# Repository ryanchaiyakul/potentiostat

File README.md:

# Potentiostat

I2BL potentiostat library and project.

# Goals

1. Create a library to easily program simple potentiostats for various voltammetry methods.
2. Create a collection of tools to develop future potentiostats.
3. Create a simulation suite to visualize and validate design decisions.

# Simulations

Go to the [README.md](CAD/LTSpice/README.md) in CAD/LTSpice folder.

# Tools

Go to the tools folder for a complete collection.

## CPE Models

Generate RC Train models of CPE elements to simulate how the readout circuit responds.

## PWL Voltammetry

Generate PWL files to pass into a voltage source to act as the DAC.

# Usage

```bash
# submodules are used in this repository for third party libraries
git clone --recurse-submodules git@github.com:ryanchaiyakul/potentiostat.git
```

1. Open the project in [VS Code](https://code.visualstudio.com/) with the [PlatformIO extension](https://marketplace.visualstudio.com/items?itemName=platformio.platformio-ide) installed.
2. Connect the Potentiostat to your computer by USB.
3. Navigate to the PlatformIO panel and click "Upload" or use the Command Palette (CNTL + SHIFT + P) and select "Upload".
4. Use the Serial Monitor in the terminal bar and select the baudrate of 230400.

# Features

- [x] Differential Pulse Voltammetry
- [x] Square Wave Voltammetry
- [ ] Cyclic Voltammetry
- [x] 300+ Hz SWV
- [ ] OTA Configuration
- [ ] EEPROM Persistent Configuration
- [ ] BLE Integration
- [x] Simple "Debug" Mode
- [x] Complete Analytics in "Debug" Mode
- [ ] Unit Testing Suite

# Development Guide

Create a valid class that inherits from Voltammetry defined in [Voltammetry.h](lib/Voltammetry/Voltammetry.h).

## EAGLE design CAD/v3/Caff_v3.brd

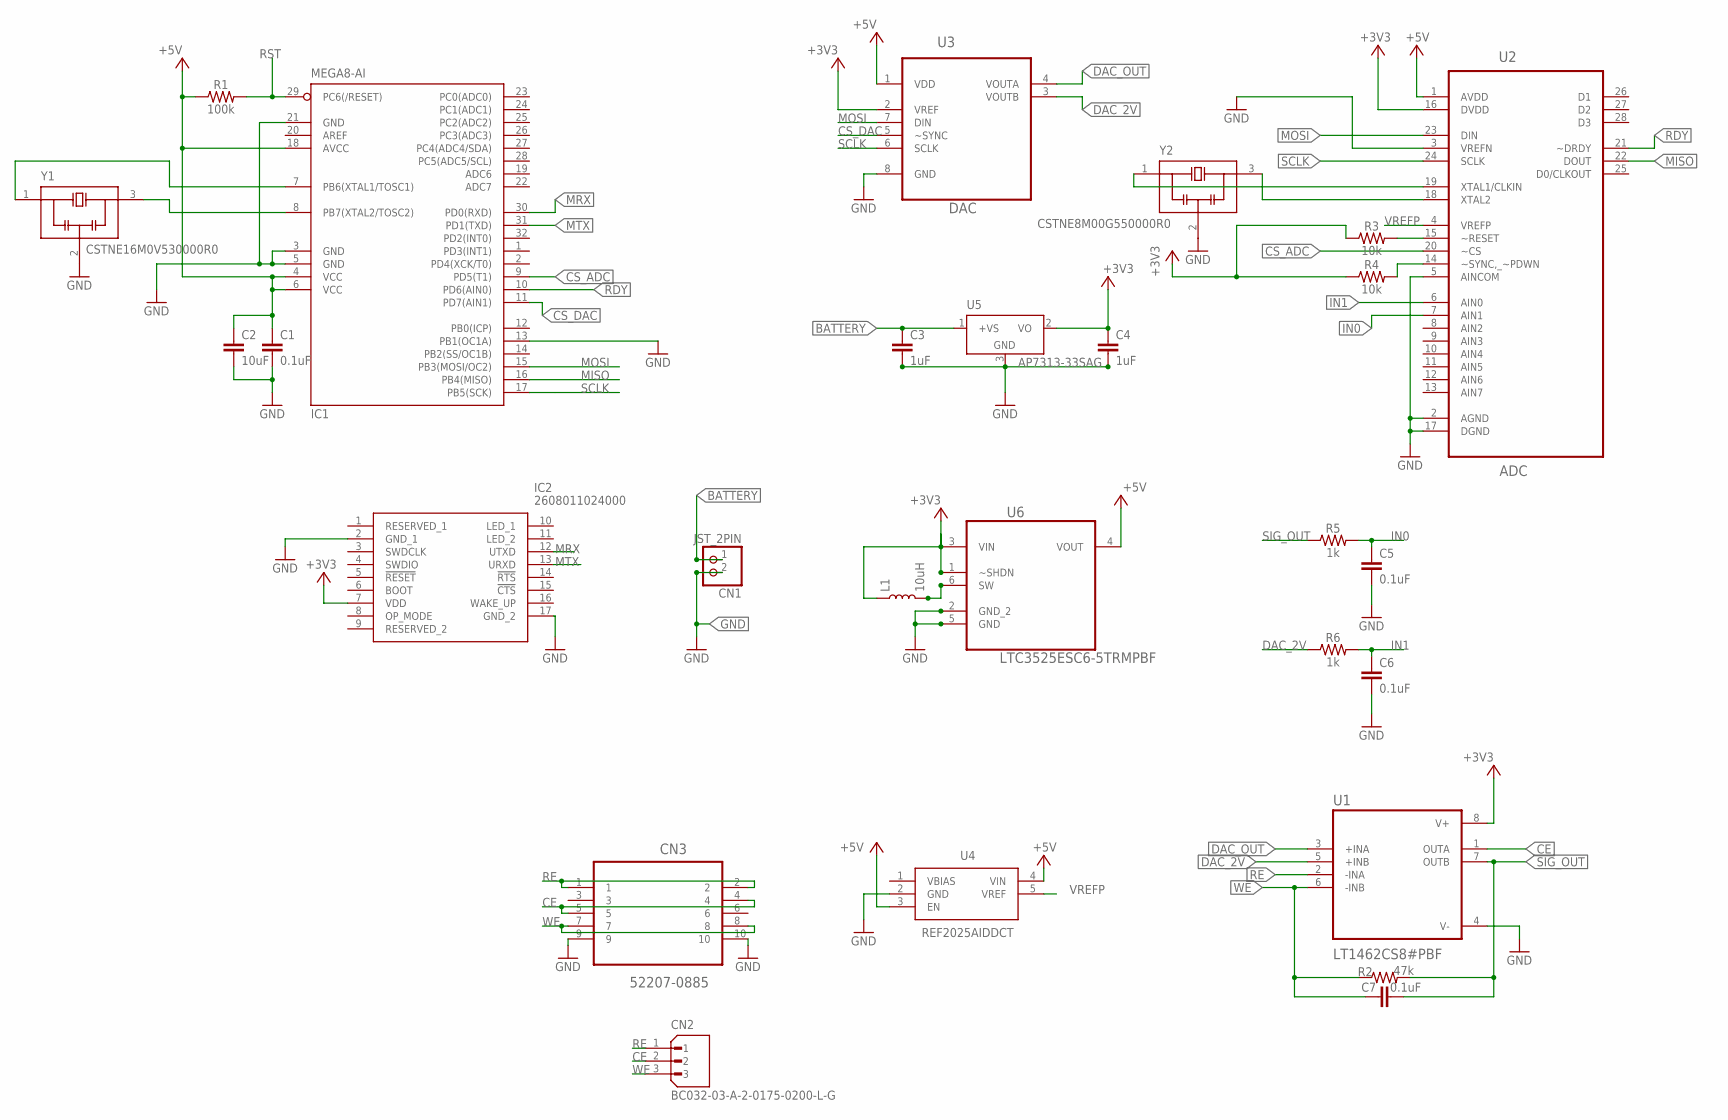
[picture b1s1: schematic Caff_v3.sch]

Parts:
C1, C5, C6, C7: 0.1uF; 0603
C2: 10uF; 0603
C3, C4: 1uF; 0603
CN1: JST_2PIN; JST-PH-2-SMT-RA
CN2: BC032-03-A-2-0175-0200-L-G; GCT_BC032-03-A-2-0175-0200-L-G
CN3: 52207-0885; MOLEX_52207-0885
IC1: MEGA8-AI; TQFP32-08
IC2: 2608011024000
L1: 10uH; 0603
R1: 100k; 0603
R2: 47k; 0603
R3, R4: 10k; 0603
R5, R6: 1k; 0603
U1: LT1462CS8#PBF; SOIC127P600X175-8N
U2: ADC; SOP65P780X200-28N
U3: DAC; SOP65P490X110-8N
U4: REF2025AIDDCT; SOT95P280X110-5N
U5: AP7313-33SAG; SOT23; MPN LM5008MM/NOPB
U6: LTC3525ESC6-5TRMPBF; SOT65P210X100-6N
Y1: CSTNE16M0V530000R0; OSC_CSTNE16M0V530000R0
Y2: CSTNE8M00G550000R0; OSC_CSTNE16M0V530000R0

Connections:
+3V3: C4.1, IC2.7 (VDD), L1.1, R3.1, R4.1, U1.8 (V+), U2.16 (DVDD), U3.2 (VREF), U5.2 (VO), U6.1 (~SHDN), U6.3 (VIN)
+5V: C1.1, C2.1, IC1.4 (VCC), IC1.6 (VCC), IC1.18 (AVCC), R1.1, U2.1 (AVDD), U3.1 (VDD), U4.3 (EN), U4.4 (VIN), U6.4 (VOUT)
BATTERY: C3.1, CN1.1 (2), U5.1 (+VS)
CE: CN2.2, CN3.4, CN3.5, U1.1 (OUTA)
CS_ADC: IC1.9 (PD5(T1)), U2.20 (~CS)
CS_DAC: IC1.11 (PD7(AIN1)), U3.5 (~SYNC)
DAC_2V: R6.1, U1.5 (+INB), U3.3 (VOUTB)
DAC_OUT: U1.3 (+INA), U3.4 (VOUTA)
GND: C1.2, C2.2, C3.2, C4.2, C5.2, C6.2, CN1.2 (1), CN3.9, CN3.10, IC1.3 (GND), IC1.5 (GND), IC1.13 (PB1(OC1A)), IC1.21 (GND), IC2.2 (GND_1), IC2.17 (GND_2), U1.4 (V-), U2.2 (AGND), U2.3 (VREFN), U2.5 (AINCOM), U2.17 (DGND), U3.8 (GND), U4.2 (GND), U5.3 (GND), U6.2 (GND_2), U6.5 (GND), Y1.2 (GND), Y2.2 (GND)
IN0: C5.1, R5.2, U2.7 (AIN1)
IN1: C6.1, R6.2, U2.6 (AIN0)
MISO: IC1.16 (PB4(MISO)), U2.22 (DOUT)
MOSI: IC1.15 (PB3(MOSI/OC2)), U2.23 (DIN), U3.7 (DIN)
MRX: IC1.30 (PD0(RXD)), IC2.12 (UTXD)
MTX: IC1.31 (PD1(TXD)), IC2.13 (URXD)
unnamed: IC1.7 (PB6(XTAL1/TOSC1)), Y1.1 (IN)
unnamed: IC1.8 (PB7(XTAL2/TOSC2)), Y1.3 (OUT)
unnamed: U2.19 (XTAL1/CLKIN), Y2.1 (IN)
unnamed: U2.18 (XTAL2), Y2.3 (OUT)
unnamed: R3.2, U2.15 (~RESET)
unnamed: L1.2, U6.6 (SW)
unnamed: R4.2, U2.14 (~SYNC,_~PDWN)
RDY: IC1.10 (PD6(AIN0)), U2.21 (~DRDY)
RE: CN2.1, CN3.1, CN3.2, U1.2 (-INA)
RST: IC1.29 (PC6(/RESET)), R1.2
SCLK: IC1.17 (PB5(SCK)), U2.24 (SCLK), U3.6 (SCLK)
SIG_OUT: C7.2, R2.2, R5.1, U1.7 (OUTB)
VREFP: U2.4 (VREFP), U4.5 (VREF)
WE: C7.1, CN2.3, CN3.7, CN3.8, R2.1, U1.6 (-INB)

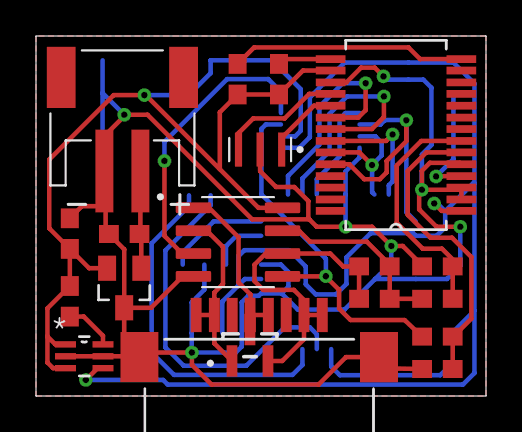
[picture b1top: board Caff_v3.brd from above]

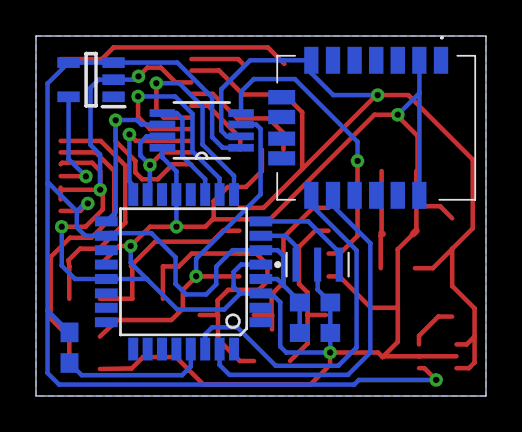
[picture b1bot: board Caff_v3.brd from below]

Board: 2 copper layers, 25.0 x 20.0 mm, 27 parts (8 on the bottom side), 29 nets.

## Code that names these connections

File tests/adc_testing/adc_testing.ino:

#include <SPI.h>
#define ADC_SPEED 2000000  // 8000000 / 4 (f_clk / 4)

// ADC Commands
#define RESET 0xFE
#define CALLIBRATE 0xF0
#define RDATA 0x01
#define RDATAC 0x03
#define SDATAC 0x0F

// Pinout
#define RDY 3
#define CS_adc 8
#define CS_dac 10
#define DIN 11   // MISO
#define DOUT 12  // MOSI
#define SCLK 13  // SCLK

int32_t ofc;
uint32_t fsc;

unsigned long ini_time;
unsigned long total_time;
uint32_t sample_counter = 150000;

uint8_t outputBuffer[3];
int count = 0;

void setup() {
  delay(50);
  // put your setup code here, to run once:
  Serial.begin(230400);
  while (!Serial) {
    ;
  }
  SPI.begin();
  pinMode(DIN, OUTPUT);   // MOSI
  pinMode(SCLK, OUTPUT);  // CLK
  pinMode(CS_adc, OUTPUT);
  digitalWrite(CS_adc, HIGH);
  pinMode(RDY, INPUT);
  pinMode(DOUT, INPUT);  // MISO

  //attachInterrupt(digitalPinToInterrupt(RDY), RDY_ISR, FALLING);

  initADS();
  printCallibration();
  ini_time = micros();
}

void loop() {
  uint32_t i = 0;
  while (i < count) {
    read_single();
    i++;
  }
  read_multi(sample_counter);
  total_time = micros() - ini_time;
  Serial.print("Total Duration (us): ");
  Serial.println(total_time);
  Serial.print("# of Samples: ");
  Serial.println(sample_counter);
  double period = double(total_time) / sample_counter;
  double frequency = (1 / period) * 1000000;
  Serial.print("Average Period (us): ");
  Serial.println(period, 6);
  Serial.print("Frequency (hz): ");
  Serial.println(frequency, 6);
  Serial.println();
  ini_time = micros();
}

// ADC

void initADS() {
  adcSendCMD(RESET);  //RESET Command
  delay(100);         //let the system power up and stabilize (datasheet pg 24)

  // ADS Settings
  adc_WR8(0x01, 0x01);  // AIN0-AIN1
  adc_WR8(0x00, 0x32);  // Enable Buffer
  adc_WR8(0x02, 0x02);  // PGA=4
  adc_WR8(0x03, 0xF0);  // DRATE=30,000SPS
  Serial.println(adc_RD8(0x01));
  Serial.println(adc_RD8(0x02));
  Serial.println(adc_RD8(0x03));
  delayMicroseconds(250);  // settling time: 30,000SPS needs 0.21ms
  callibrateADS();
}

void callibrateADS() {
  adcSendCMD(CALLIBRATE);  //send the calibration command
  delayMicroseconds(800);  // roughly 692 us for 30,000SPS PGA=4

  waitforDRDY();  // Wait until DRDY is LOW => calibration complete
  uint8_t off0 = adc_RD8(0x05);
  uint8_t off1 = adc_RD8(0x06);
  uint8_t off2 = adc_RD8(0x07);
  uint8_t fs0 = adc_RD8(0x08);
  uint8_t fs1 = adc_RD8(0x09);
  uint8_t fs2 = adc_RD8(0x0A);

  ofc = (off2 << 16 & 0x00FF0000) | off1 << 8 | off0;  // already sign-extends from 24 bits
  fsc = fs2;                                           // fsc = (fs2 << 16 & 0x00FF0000) | fs1 << 8 | fs0; idk why it breaks?? but it does
  fsc = (fsc << 8) + fs1;
  fsc = (fsc << 8) + fs0;
}

void printCallibration() {
  Serial.print(ofc);
  Serial.print(",");
  Serial.println(fsc);
}

/**
   Blocks until DRDY falls
*/
void waitforDRDY() {
  while(digitalRead(RDY)) {
    continue;
  }
}

void read_multi(uint32_t count) {
  SPI.beginTransaction(SPISettings(ADC_SPEED, MSBFIRST, SPI_MODE1));
  digitalWrite(CS_adc, LOW);  //Pull SS Low to Enable Communications with ADS1247
  waitforDRDY(); //Wait until DRDY does low, then issue the command
  SPI.transfer(RDATAC);
  delayMicroseconds(7); //Wait t6 time (~6.51 us) REF: P34, FIG:30.

  uint32_t i = 0;
  while (i < count) {
    waitforDRDY();
    outputBuffer[0] = SPI.transfer(0);
    outputBuffer[1] = SPI.transfer(0);
    outputBuffer[2] = SPI.transfer(0);
    //Serial.write(outputBuffer, 3);
    //Serial.write('\n');
    i++;
  }
  SPI.transfer(SDATAC);
  digitalWrite(CS_adc, HIGH);
  SPI.endTransaction();
}

int32_t read_single() {
  int32_t adc_val;
  SPI.beginTransaction(SPISettings(ADC_SPEED, MSBFIRST, SPI_MODE1));
  digitalWrite(CS_adc, LOW);  //Pull SS Low to Enable Communications with ADS1247
  waitforDRDY();  // Wait until DRDY is LOW
  SPI.transfer(RDATA);         // Issue read data command RDATA
  delayMicroseconds(7);

  // assemble 3 bytes into one 32 bit word
  adc_val = ((uint32_t)SPI.transfer(0) << 16) & 0x00FF0000;
  adc_val |= ((uint32_t)SPI.transfer(0) << 8);
  adc_val |= SPI.transfer(0);

  digitalWrite(CS_adc, HIGH);
  SPI.endTransaction();

  //  Extend a signed number
  if (adc_val & 0x800000) {
    adc_val |= 0xFF000000;
  }
  return adc_val;
}

void adc_WR8(byte addr, uint8_t data) {
  SPI.beginTransaction(SPISettings(ADC_SPEED, MSBFIRST, SPI_MODE1));
  digitalWrite(CS_adc, LOW);
  delayMicroseconds(5);
  SPI.transfer(0x50 | addr);
  SPI.transfer(0x00);
  SPI.transfer(data);
  digitalWrite(CS_adc, HIGH);
  SPI.endTransaction();
}

uint8_t adc_RD8(byte addr) {
  uint8_t bufr;
  SPI.beginTransaction(SPISettings(ADC_SPEED, MSBFIRST, SPI_MODE1));
  digitalWrite(CS_adc, LOW);
  SPI.transfer(0x10 | addr);  // send 1st command byte, address of the register
  SPI.transfer(0x00);         // send 2nd command byte, read only one register
  delayMicroseconds(5);
  bufr = SPI.transfer(0);  // read data of the register
  digitalWrite(CS_adc, HIGH);
  SPI.endTransaction();
  return bufr;
}

void adcSendCMD(uint8_t cmd) {
  SPI.beginTransaction(SPISettings(ADC_SPEED, MSBFIRST, SPI_MODE1));
  digitalWrite(CS_adc, LOW);
  SPI.transfer(cmd);
  digitalWrite(CS_adc, HIGH);
  SPI.endTransaction();
}

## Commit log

2023-08-09 initial commit
    working DPV
2023-08-09 somewhat working version
2023-08-11 working swv and dpv
2023-08-15 added settings
2023-08-15 switched to nonblocking design
2023-08-18 working copy
2023-08-18 basic readme
2023-08-18 fixed minor comments
2023-08-21 renamed .ino file
    Arduino IDE does not like files not named after the folder they are in
2023-08-21 added testing suite
    Still need to make comments and refine
2023-08-23 working 30k sps ADC
2023-08-25 working master with 30k SPS
2023-08-25 added .ipynb
2023-10-21 initial commit
    Working DPV and SWV configured by fixed variables. Contains basic
    LTSpice for TransAmp calculations. Use with VS Code and Platform.io.
2023-10-21 documentation
    Created README.md for the overall project
2023-10-21 CAD populated
    Moved transAmp into folder and brought back v3 Eagle design
2023-10-21 Update platformio.yml
    Added submodules
2023-10-21 Update platformio.yml
    round 2 of submodules
2023-10-21 Update README.md
    Added markdown badge for CI
2024-01-08 starting transamp
2024-01-12 migrated LTSpice files
    Moved and renamed LTSpice files into corresponding folder with .plt
    forms
2024-04-09 working DAC80502
    The SPI works but it is intermittent
2024-04-13 cleaned up workspace
    Added documentation and finalized folder structure
2024-04-13 removed excess import guides
2024-04-26 pushing wip LMP910000
2024-12-16 final
2025-01-31 add CPE back

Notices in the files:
parts and their libraries:
SparkFun-Capacitors: Licensing: Creative Commons ShareAlike 4.0 International - https://creativecommons.org/licenses/by-sa/4.0
